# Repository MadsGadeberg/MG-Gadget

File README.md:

English README
Features that the controller has.
Lock/unlock
The motorcycle can be locked and unlocked using key combinations with the right and left push buttons.
To unlock/turn on the motorcycle, press both buttons down, then release the right one, followed by pressing both buttons down again.
To lock the motorcycle, use the aforementioned combination in reverse. That is, release and press the left button. These combinations will of course be changed before the final version.

When turning on/off, the turn signals blink with different numbers of flashes, providing confirmation whether the motorcycle is off or on.

Both the right and left buttons have 2 different functions depending on whether you press them or hold them down. These functions can be inverted by using the "config0" port. This is useful if, for example, you have a motorcycle without turn signals. Then you would like to have some other functions upon a normal press instead of the turn signals.

Left push button
A press turns the driving light off/on.
Holding the button down triggers the blinkers.
These functions can be inverted by setting the "config0" port to plus.
If the motorcycle is off, the position light can be turned on by holding down the left push button.

Right push button
A press switches between low/high beam.
Holding the button down activates the blinkers.
These functions can also be inverted by setting the "config0" port to plus.

Right and Left
Pressing both buttons cuts the power to the ignition coils for 5 seconds. "Engine Kill"

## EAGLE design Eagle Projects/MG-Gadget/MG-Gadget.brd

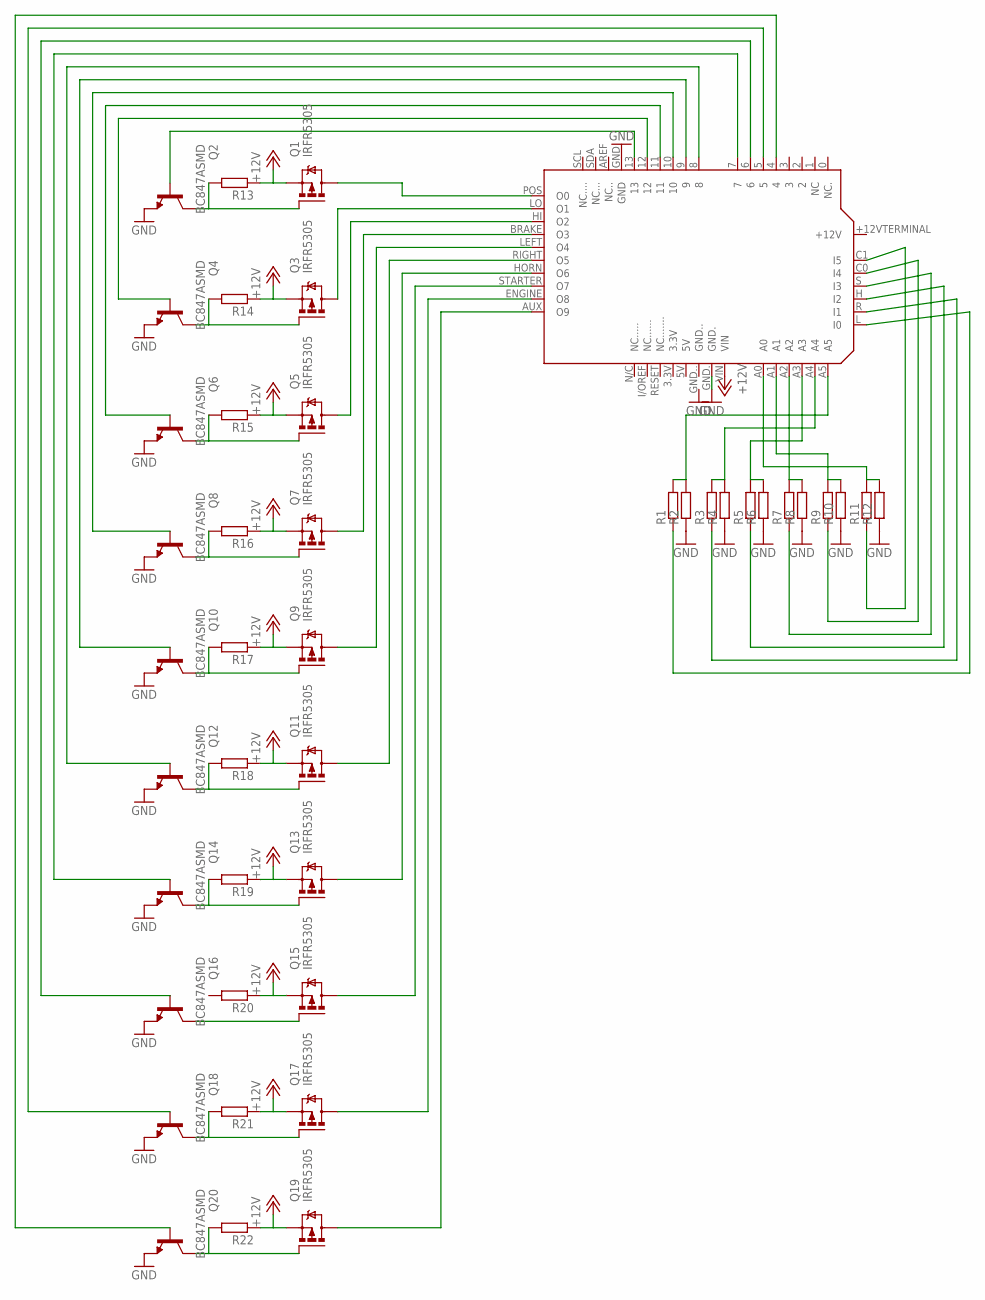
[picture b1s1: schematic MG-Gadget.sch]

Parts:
PCB1: ARDUINO_UNO
Q1, Q3, Q5, Q7, Q9, Q11, Q13, Q15, Q17, Q19: IRFR5305; D-PAK_TO252AA
Q2, Q4, Q6, Q8, Q10, Q12, Q14, Q16, Q18, Q20: BC847ASMD; SOT23
R1, R2, R3, R4, R5, R6, R7, R8, R9, R10, R11, R12, R13, R14, R15, R16, R17, R18, R19, R20, R21, R22: R-EU_R0805; R0805

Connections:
+12V: PCB1.+12VTERMINAL (+12V), PCB1.VIN, Q1.3 (S), Q3.3 (S), Q5.3 (S), Q7.3 (S), Q9.3 (S), Q11.3 (S), Q13.3 (S), Q15.3 (S), Q17.3 (S), Q19.3 (S), R13.1, R14.1, R15.1, R16.1, R17.1, R18.1, R19.1, R20.1, R21.1, R22.1
GND: PCB1.GND, PCB1.GND., Q2.2 (E), Q4.2 (E), Q6.2 (E), Q8.2 (E), Q10.2 (E), Q12.2 (E), Q14.2 (E), Q16.2 (E), Q18.2 (E), Q20.2 (E), R2.1, R4.1, R6.1, R8.1, R10.1, R12.1
unnamed: PCB1.A5, R1.2, R2.2
unnamed: PCB1.A4, R3.2, R4.2
unnamed: PCB1.A3, R5.2, R6.2
unnamed: PCB1.A2, R7.2, R8.2
unnamed: PCB1.A1, R9.2, R10.2
unnamed: PCB1.A0, R11.2, R12.2
unnamed: PCB1.C1 (I5), R11.1
unnamed: PCB1.C0 (I4), R9.1
unnamed: PCB1.S (I3), R7.1
unnamed: PCB1.H (I2), R5.1
unnamed: PCB1.R (I1), R3.1
unnamed: PCB1.L (I0), R1.1
unnamed: Q1.1 (G), Q2.3 (C), R13.2
unnamed: PCB1.POS (O0), Q1.4 (D)
unnamed: Q3.1 (G), Q4.3 (C), R14.2
unnamed: Q5.1 (G), Q6.3 (C), R15.2
unnamed: PCB1.13, Q2.1 (B)
unnamed: Q7.1 (G), Q8.3 (C), R16.2
unnamed: PCB1.12, Q4.1 (B)
unnamed: Q9.1 (G), Q10.3 (C), R17.2
unnamed: PCB1.11, Q6.1 (B)
unnamed: Q11.1 (G), Q12.3 (C), R18.2
unnamed: PCB1.10, Q8.1 (B)
unnamed: Q13.1 (G), Q14.3 (C), R19.2
unnamed: PCB1.9, Q10.1 (B)
unnamed: Q15.1 (G), Q16.3 (C)
unnamed: PCB1.8, Q12.1 (B)
unnamed: Q17.1 (G), Q18.3 (C), R21.2
unnamed: PCB1.7, Q14.1 (B)
unnamed: Q19.1 (G), Q20.3 (C), R22.2
unnamed: PCB1.6, Q16.1 (B)
unnamed: PCB1.LO (O1), Q3.4 (D)
unnamed: PCB1.HI (O2), Q5.4 (D)
unnamed: PCB1.BRAKE (O3), Q7.4 (D)
unnamed: PCB1.LEFT (O4), Q9.4 (D)
unnamed: PCB1.RIGHT (O5), Q11.4 (D)
unnamed: PCB1.HORN (O6), Q13.4 (D)
unnamed: PCB1.STARTER (O7), Q15.4 (D)
unnamed: PCB1.ENGINE (O8), Q17.4 (D)
unnamed: PCB1.AUX (O9), Q19.4 (D)
unnamed: PCB1.5, Q18.1 (B)
unnamed: PCB1.4, Q20.1 (B)

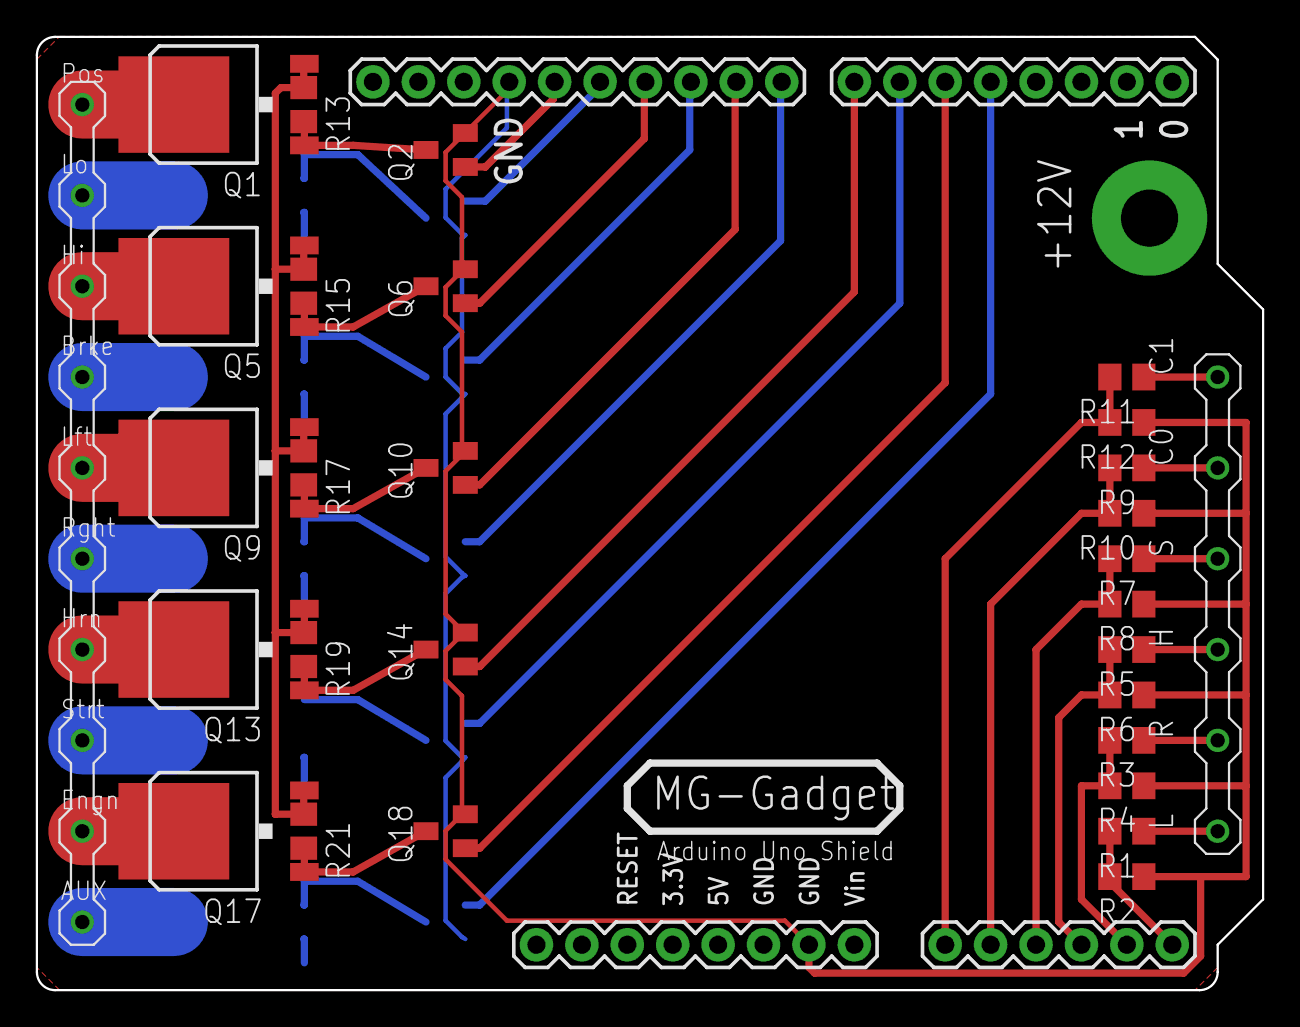
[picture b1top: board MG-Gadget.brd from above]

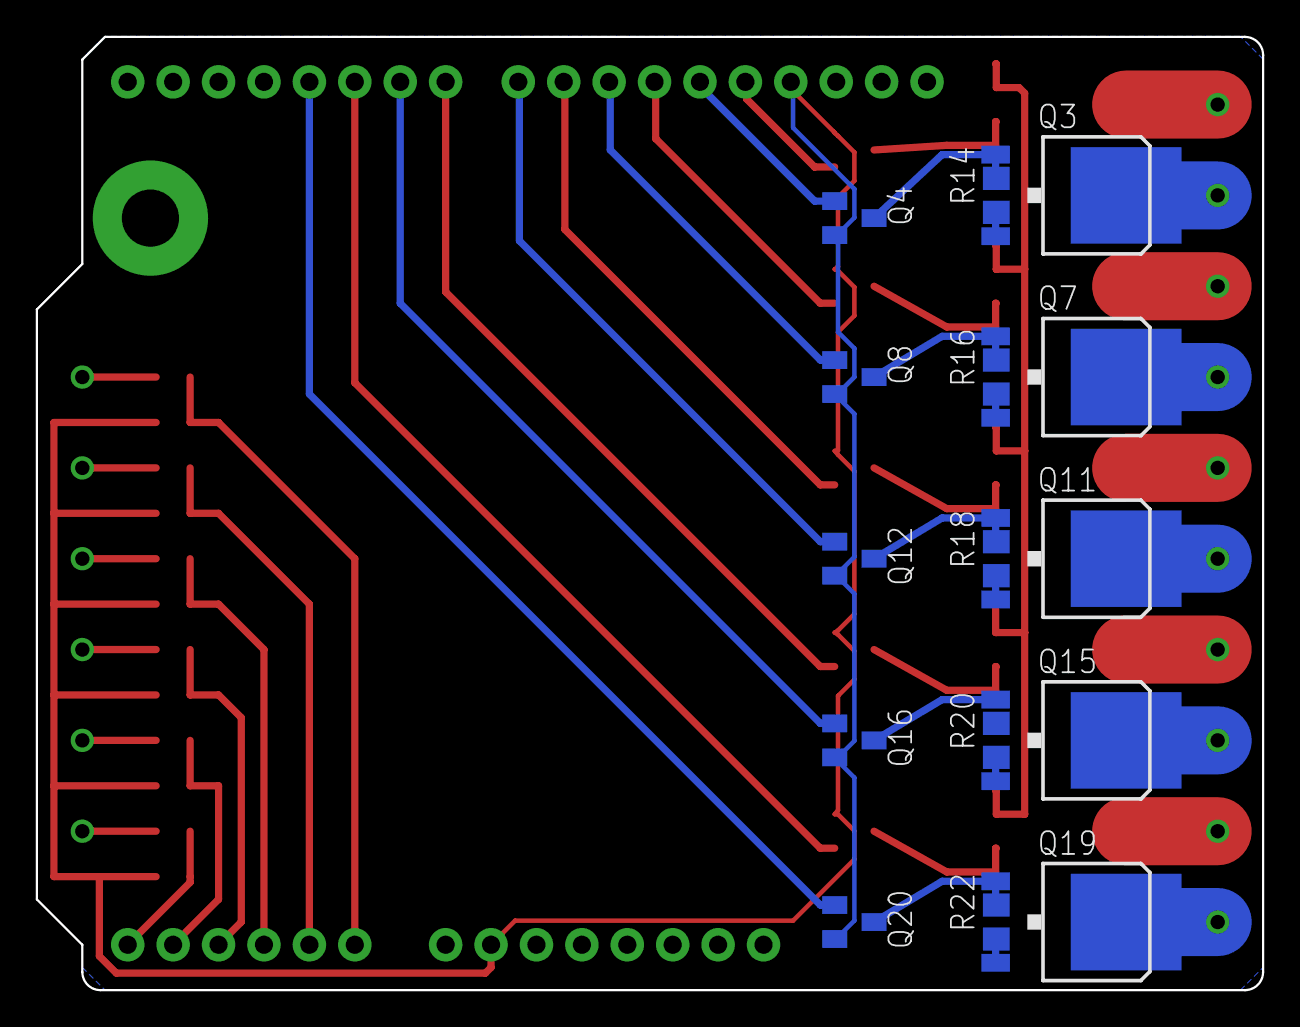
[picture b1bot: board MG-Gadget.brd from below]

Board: 2 copper layers, 68.6 x 53.3 mm, 43 parts (15 on the bottom side), 44 nets.

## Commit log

2016-06-18 Initial commit, that contains a final version of the software besides some Arduino functionalities that should be fixed before uploading to the chip. This code is meant for an arduino that shares the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
2016-06-18 Readme updated with Danish functionality explanations.
2016-06-19 smth that doesent matter
2016-06-20 Get portD made with debouncer.
2016-06-20 Debouncetime corrected
2016-06-21 Added drawings of the motorcycle and the controller board.
2016-06-21 Added ATmega 328p documentation.
2016-06-24 Read function
2016-06-24 Cleanup and small fixes
2016-06-28 Updated pin numbers and cleaned for temporary test settings
2016-06-28 Repo Clean, Added board drawings.
2016-06-28 Removed Shiftregister Debounce since it is not needed due to Standard time debounde functionality.
2016-06-29 Fixed Config input functionality and some mort numbering for Arduino uno usage.
2016-06-29 Merge
2016-06-29 Smarter port filter edits
2016-06-30 Main lights fix.
2016-07-08 Added Eagle projects of Arduino shield
2016-07-11 New smaller PCB board using Arduino Pro Mini
2016-07-23 Eagle files
2016-07-26 Target pin numbering update, along with deleting of serial messages for debugging
